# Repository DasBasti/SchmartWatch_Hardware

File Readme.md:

# Schmart Watch Hardware

## Table of Contents

- [Introduction](#introduction)
- [Terms of Use](#terms-of-use)
- [Problems?](#problems)
- [Changelog](#changelog)

## Introduction

This application is the hardware for the DIY Smartwatch project [Schmart Watch](http://www.kurzschluss-blog.de/2018/07/schmartwatch-01-smartwatch-selbst-gebaut.html).

To open the project you need [KiCad Version 5.0.0-rc2](http://kicad.org/) or newer.

## Terms of Use

Refer to "License.txt" for terms of use.

## Problems?

If you have any problems or questions, please ensure you have read this readme
file. If you are still having trouble, you can
[get in contact](https://plus.google.com/+BastianNeumann_DasBasti).

## Changelog

1. 2019-02-20: Version 0.1
  - Initial release of hardware version E3 for review

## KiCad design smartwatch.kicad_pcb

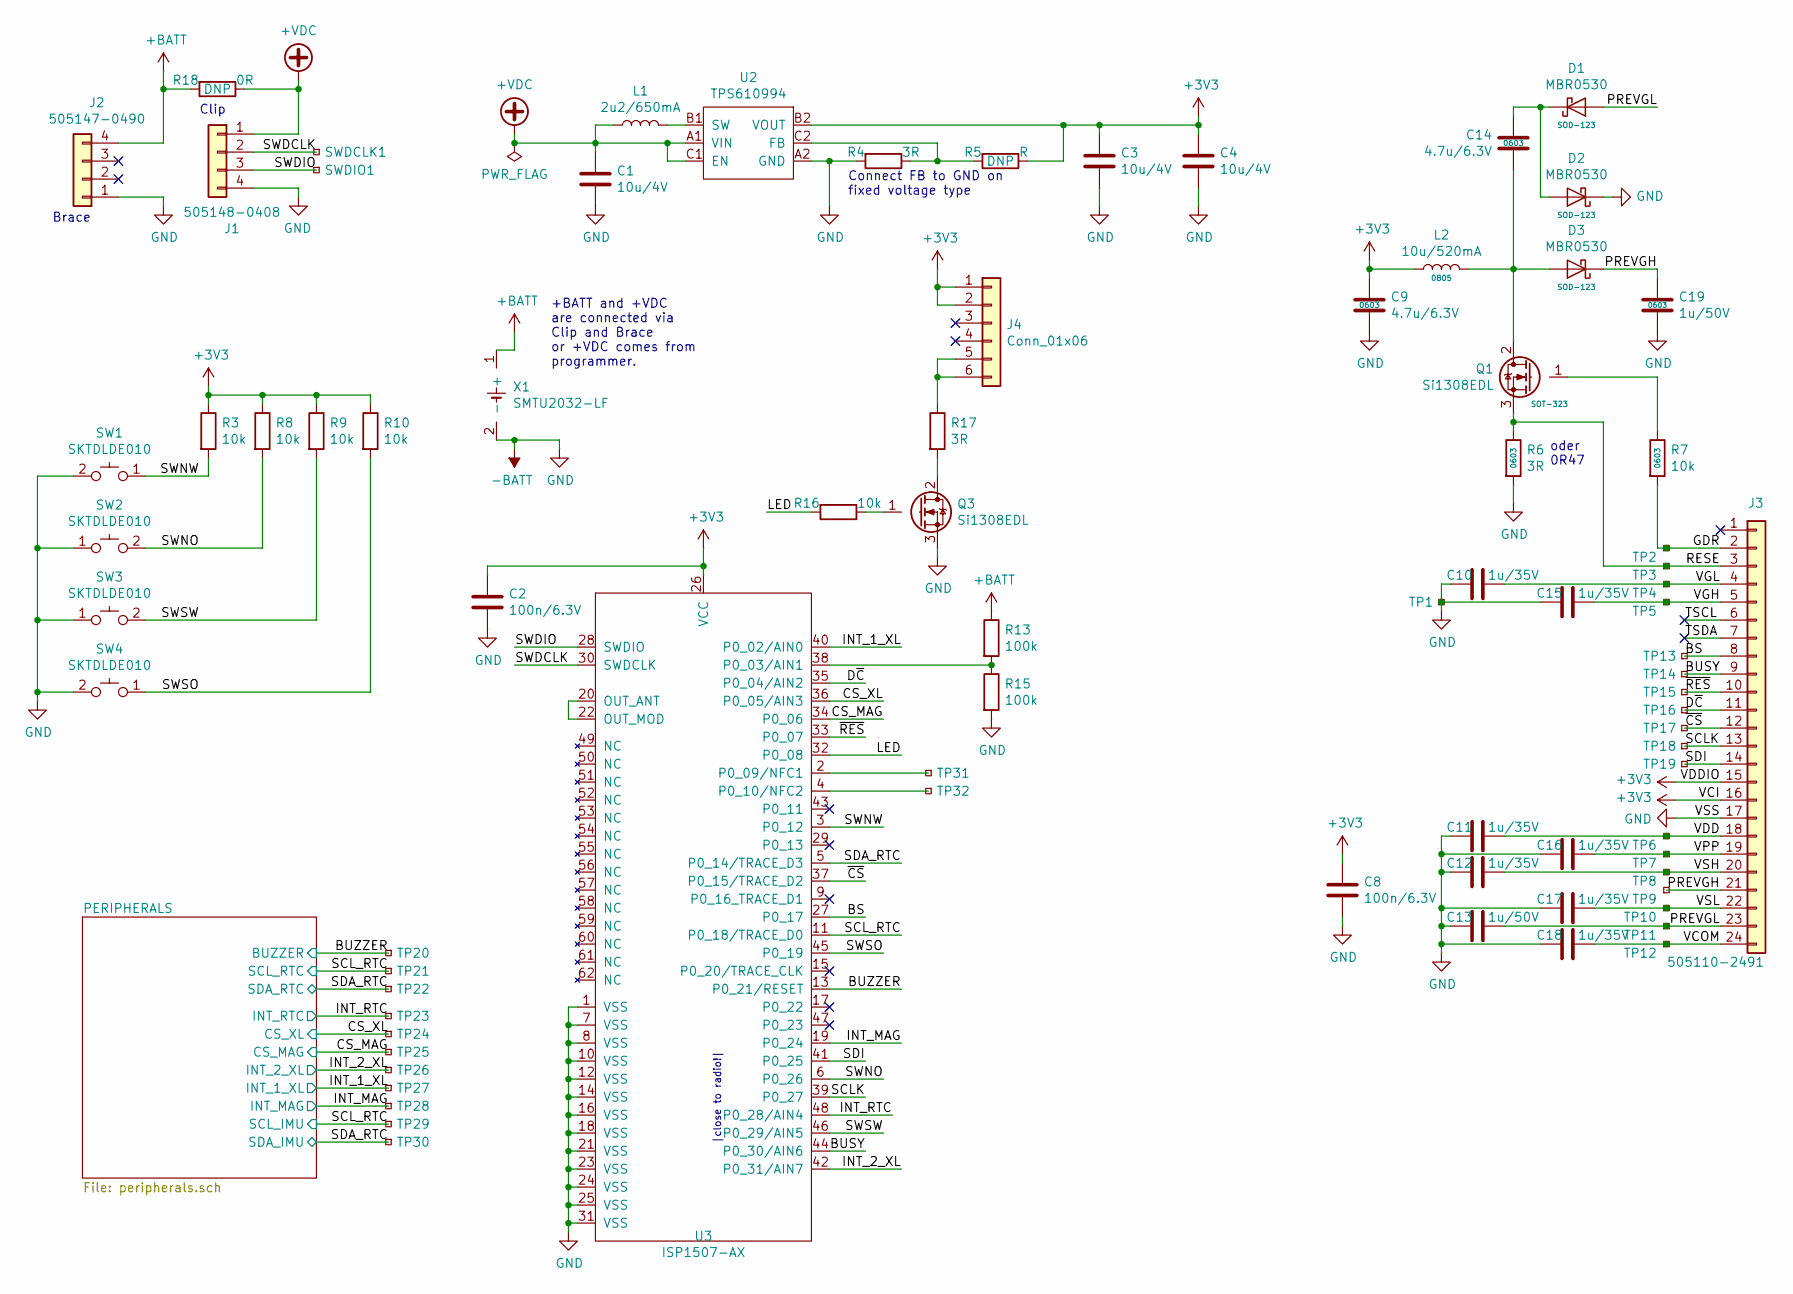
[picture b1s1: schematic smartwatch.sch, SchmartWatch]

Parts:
C1, C3, C4: 10u/4V; C_0603_1608Metric; MPN1 CL10A106MQ8NNNC
C2, C8: 100n/6.3V; C_0603_1608Metric; MPN1 GCM188R71C104KA37D
C9, C14: 4.7u/6.3V; C_0603_1608Metric; MPN1 GRT188C80J475ME01D
C10, C11, C12, C15, C16, C17, C18: 1u/35V; C_0603_1608Metric; MPN1 C1608X7R1V105K080AC
C13, C19: 1u/50V; C_0603_1608Metric; MPN1 GRT188R61H105KE13D
D1, D2, D3: MBR0530; D_SOD-123; MPN1 MBR0530
J1: 505148-0408; MPN1 505148-0408
J2: 505147-0490; 505147-0490_NO_SOLDER; MPN1 505147-0490
J3: 505110-2491; MOLEX_FPC_24_P0.5mm_505110-2491; MPN1 505110-2491
J4: Conn_01x06; 503480-0600; MPN1 503480-0600
L1: 2u2/650mA; L_0805_2012Metric; MPN1 MBKK2012T2R2M
L2: 10u/520mA; L_0805_2012Metric; MPN1 CB2012T100KR
Q1, Q3: Si1308EDL; SOT-323_SC-70; MPN1 SI1308EDL-T1-GE3
R3, R7, R8, R9, R10, R16: 10k; R_0603_1608Metric; MPN1 RMCF0603JG10K0
R4, R6, R17: 3R; R_0603_1608Metric; MPN1 RMCF0603JT3R00
R5: R; R_0603_1608Metric
R13, R15: 100k; R_0603_1608Metric; MPN1 RMCF0603JG100K
R18: 0R; R_0603_1608Metric
SW1, SW2, SW3, SW4: SKTDLDE010; MPN1 SKTDLDE010
SWDCLK1: TestPoint; TestPoint_Pad_D1.0mm
SWDIO1: TestPoint; TestPoint_Pad_D1.0mm
TP1, TP2, TP3, TP4, TP5, TP6, TP7, TP8, TP9, TP10, TP11, TP12, TP13, TP14, TP15, TP16, TP17, TP18, TP19, TP20, TP21, TP22, TP23, TP28, TP29, TP30: TestPoint; TestPoint_Pad_D1.0mm
TP24, TP25, TP26, TP27, TP31, TP32: TestPoint; TestPoint_Pad_D0.5mm
U2: TPS610994; BGA-6_2x3_1.0x1.35mm; MPN1 TPS610994
U3: ISP1507-AX; MPN1 ISP1507-AX
X1: SMTU2032-LF; SMTU2032-LF-6066; MPN1 SMTU2032-LF

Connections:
+3V3: C2.1, C3.1, C4.1, C8.1, C9.1, J3.15, J3.16, J3.25, J3.26, J4.1, J4.2, J4.7, J4.8, L2.1, R3.1, R5.1, R8.1, R9.1, R10.1, U2.B2 (VOUT), U3.26 (VCC); also elsewhere on the board
+BATT: J2.4, R13.1, R18.2, X1.1 (+); also elsewhere on the board
+VDC: C1.1, J1.1, L1.1, R18.1, U2.A1 (VIN), U2.C1 (EN)
-BATT: C1.2, C2.2, C3.2, C4.2, C8.2, C9.2, C10.2, C11.2, C12.2, C13.2, C15.2, C16.2, C17.2, C18.2, C19.2, D2.1 (K), J1.4, J2.1, J3.17, Q3.3 (S), R4.2, R6.2, R15.2, SW1.2, SW2.1, SW3.1, SW4.2, TP1.1, U2.A2 (GND), U3.1 (VSS), U3.7 (VSS), U3.8 (VSS), U3.10 (VSS), U3.12 (VSS), U3.14 (VSS), U3.16 (VSS), U3.18 (VSS), U3.21 (VSS), U3.23 (VSS), U3.24 (VSS), U3.25 (VSS), U3.31 (VSS), X1.2 (-); also elsewhere on the board
/BS: J3.8, TP13.1, U3.27 (P0_17)
/BUSY: J3.9, TP14.1, U3.44 (P0_30/AIN6)
/BUZZER: TP20.1, U3.13 (P0_21/RESET); also elsewhere on the board
/CS_MAG: TP25.1, U3.34 (P0_06); also elsewhere on the board
/CS_XL: TP24.1, U3.36 (P0_05/AIN3); also elsewhere on the board
/D~C: J3.11, TP16.1, U3.35 (P0_04/AIN2)
/GDR: J3.2, R7.2, TP2.1
/INT_1_XL: TP27.1, U3.40 (P0_02/AIN0); also elsewhere on the board
/INT_2_XL: TP26.1, U3.42 (P0_31/AIN7); also elsewhere on the board
/INT_MAG: TP28.1, U3.19 (P0_24); also elsewhere on the board
/INT_RTC: TP23.1, U3.48 (P0_28/AIN4); also elsewhere on the board
/LED: R16.2, U3.32 (P0_08)
/PREVGH: C19.1, D3.1 (K), J3.21, TP9.1
/PREVGL: C13.1, D1.2 (A), J3.23, TP11.1
/RESE: J3.3, Q1.3 (S), R6.1, TP3.1
/SCLK: J3.13, TP18.1, U3.39 (P0_27)
/SCL_RTC: TP21.1, TP29.1, U3.11 (P0_18/TRACE_D0); also elsewhere on the board
/SDA_RTC: TP22.1, TP30.1, U3.5 (P0_14/TRACE_D3); also elsewhere on the board
/SDI: J3.14, TP19.1, U3.41 (P0_25)
/SWDCLK: J1.2, SWDCLK1.1, U3.30 (SWDCLK)
/SWDIO: J1.3, SWDIO1.1, U3.28 (SWDIO)
/SWNO: R8.2, SW2.2, U3.6 (P0_26)
/SWNW: R3.2, SW1.1, U3.3 (P0_12)
/SWSO: R10.2, SW4.1, U3.45 (P0_19)
/SWSW: R9.2, SW3.2, U3.46 (P0_29/AIN5)
/TSCL: J3.6
/TSDA: J3.7
/VCOM: C18.1, J3.24, TP12.1
/VDD: C11.1, J3.18, TP6.1
/VGH: C15.1, J3.5, TP5.1
/VGL: C10.1, J3.4, TP4.1
/VPP: C16.1, J3.19, TP7.1
/VSH: C12.1, J3.20, TP8.1
/VSL: C17.1, J3.22, TP10.1
/~CS: J3.12, TP17.1, U3.37 (P0_15/TRACE_D2)
/~RES: J3.10, TP15.1, U3.33 (P0_07)
unnamed: C14.1, D1.1 (K), D2.2 (A)
unnamed: C14.2, D3.2 (A), L2.2, Q1.2 (D)
unnamed 43: J2.2; also elsewhere on the board
unnamed 44: J2.3; also elsewhere on the board
unnamed: J4.5, J4.6, R17.1
unnamed: L1.2, U2.B1 (SW)
unnamed: Q1.1 (G), R7.1
unnamed: Q3.1 (G), R16.1
unnamed: Q3.2 (D), R17.2
unnamed: R4.1, R5.2, U2.C2 (FB)
unnamed: R13.2, R15.1, U3.38 (P0_03/AIN1)
unnamed: TP31.1, U3.2 (P0_09/NFC1)
unnamed: TP32.1, U3.4 (P0_10/NFC2)
unnamed: U3.20 (OUT_ANT), U3.22 (OUT_MOD)

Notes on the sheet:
|close to radio!|
oder 0R47
Clip
Brace
+BATT and +VDC are connected via Clip and Brace or +VDC comes from programmer.
Connect FB to GND on fixed voltage type

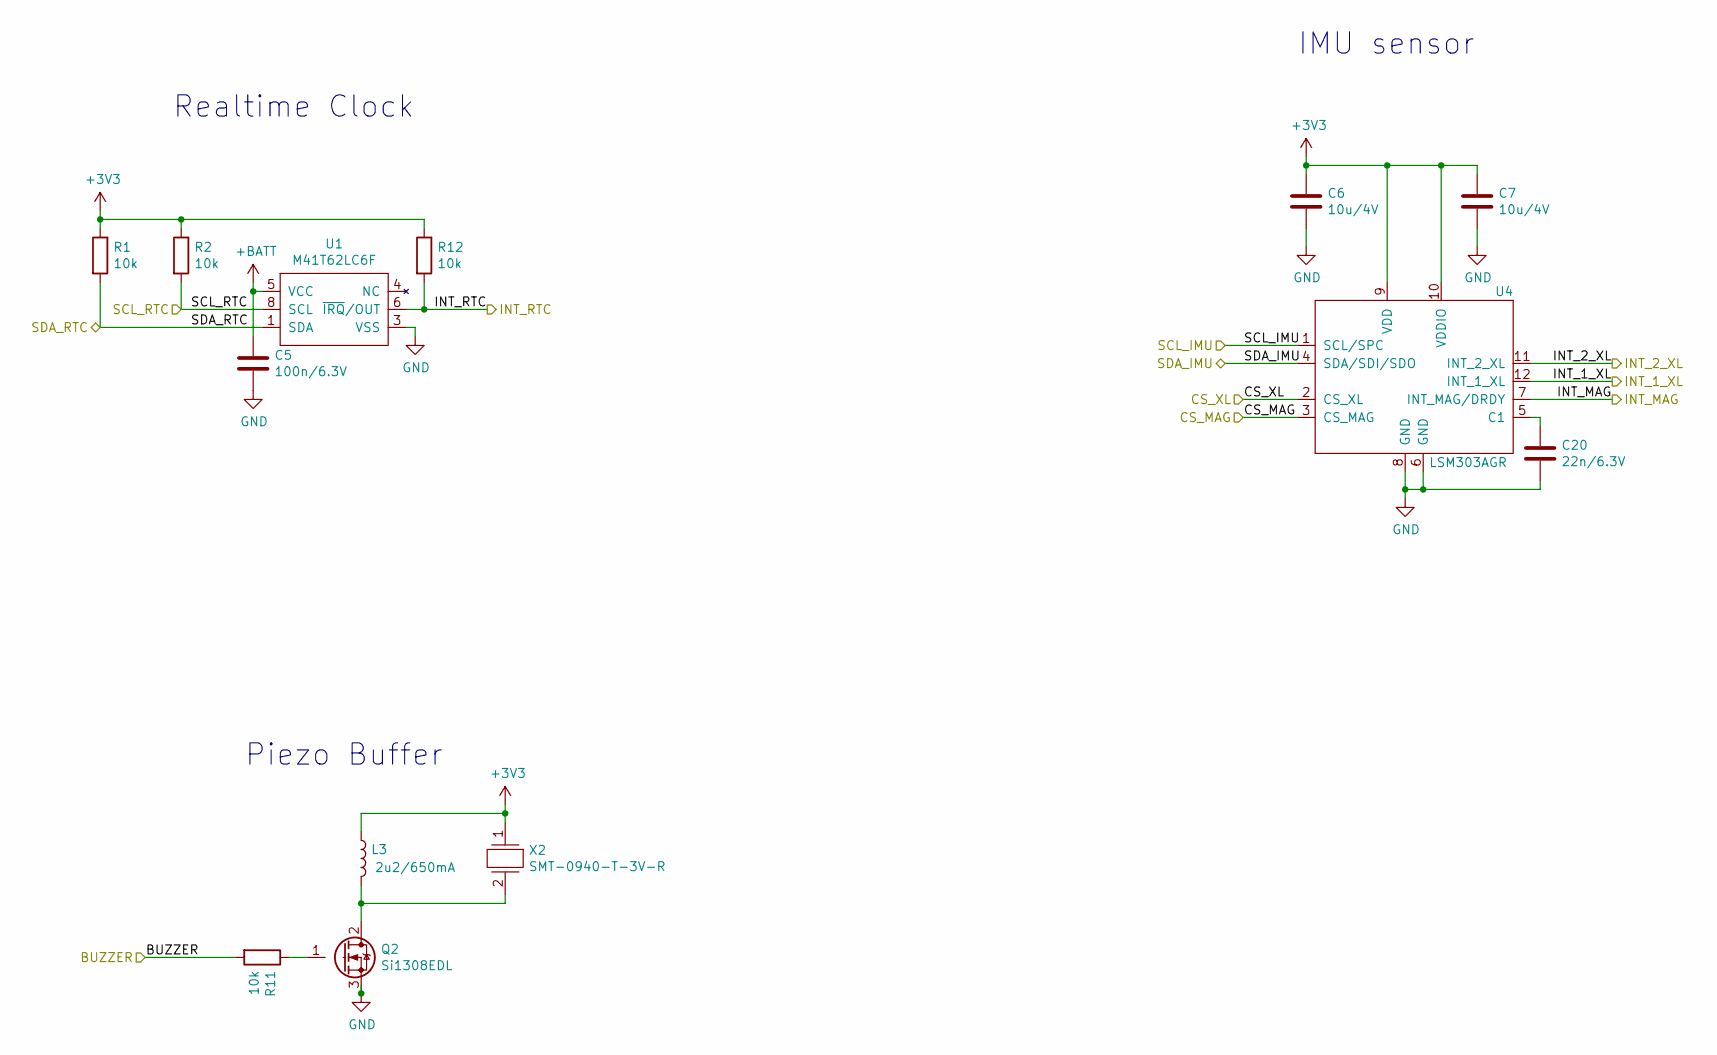
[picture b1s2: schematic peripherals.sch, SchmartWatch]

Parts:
C5: 100n/6.3V; C_0603_1608Metric; MPN1 GCM188R71C104KA37D
C6, C7: 10u/4V; C_0603_1608Metric; MPN1 CL10A106MQ8NNNC
C20: 22n/6.3V; C_0603_1608Metric; MPN1 GRM188R71H223KA01D
L3: 2u2/650mA; L_0805_2012Metric; MPN1 MBKK2012T2R2M
Q2: Si1308EDL; SOT-323_SC-70; MPN1 SI1308EDL-T1-GE3
R1, R2, R11, R12: 10k; R_0603_1608Metric; MPN1 RMCF0603JG10K0
U1: M41T62LC6F; LCC-8_1.5x3.2mm_P0.9mm; MPN1 M41T62LC6F
U4: LSM303AGR; LGA-12_2x2mm_P0.5mm; MPN1 LSM303AGR
X2: SMT-0940-T-3V-R; SMT-0940-T_3V-R; MPN1 SMT-0940-T-3V-R

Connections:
+3V3: C6.1, C7.1, L3.1, R1.1, R2.1, R12.1, U4.9 (VDD), U4.10 (VDDIO), X2.1; also elsewhere on the board
+BATT: C5.1, U1.5 (VCC); also elsewhere on the board
-BATT: C5.2, C6.2, C7.2, C20.2, Q2.3 (S), U1.3 (VSS), U4.6 (GND), U4.8 (GND); also elsewhere on the board
/BUZZER: R11.2; also elsewhere on the board
/CS_MAG: U4.3 (CS_MAG); also elsewhere on the board
/CS_XL: U4.2 (CS_XL); also elsewhere on the board
/INT_1_XL: U4.12 (INT_1_XL); also elsewhere on the board
/INT_2_XL: U4.11 (INT_2_XL); also elsewhere on the board
/INT_MAG: U4.7 (INT_MAG/DRDY); also elsewhere on the board
/INT_RTC: R12.2, U1.6 (~IRQ~/OUT); also elsewhere on the board
/SCL_RTC: R2.2, U1.8 (SCL), U4.1 (SCL/SPC); also elsewhere on the board
/SDA_RTC: R1.2, U1.1 (SDA), U4.4 (SDA/SDI/SDO); also elsewhere on the board
unnamed: C20.1, U4.5 (C1)
unnamed: L3.2, Q2.2 (D), X2.2
unnamed: Q2.1 (G), R11.1

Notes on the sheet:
Realtime Clock
IMU sensor
Piezo Buffer

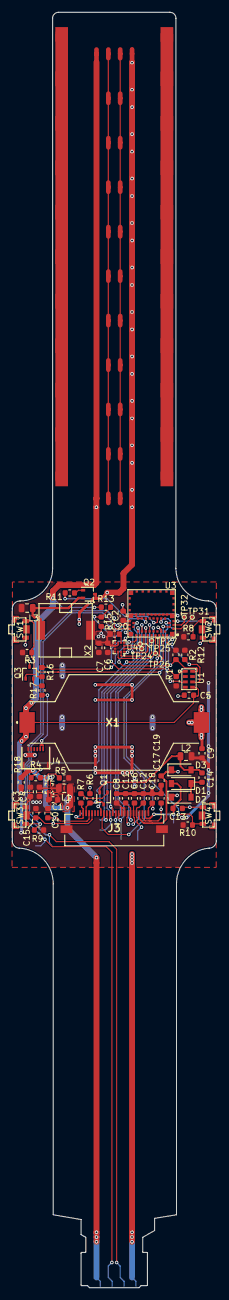
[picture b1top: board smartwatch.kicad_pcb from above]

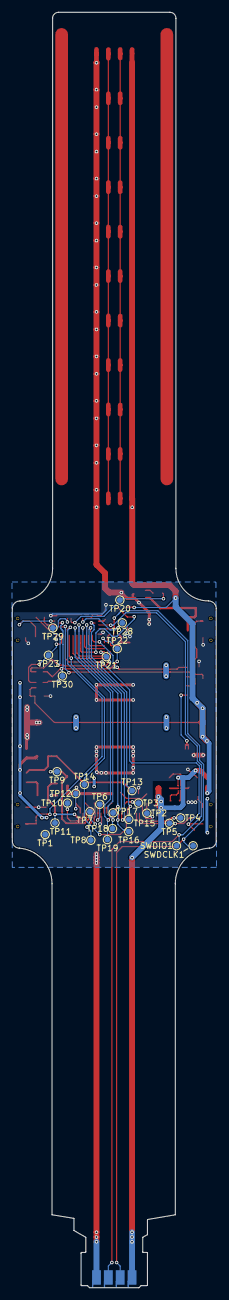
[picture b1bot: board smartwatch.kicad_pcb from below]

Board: 2 copper layers, 34.4 x 215.2 mm, 104 parts (29 on the bottom side), 55 nets.

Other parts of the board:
J2#2, J2#3, J2#4, J2#5, J2#6, J2#7, J2#8, J2#9, J2#10, J2#11: 505147-0490; 505147-0490_NO_SOLDER

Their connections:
+BATT: J2#2.4, J2#3.4, J2#4.4, J2#5.4, J2#6.4, J2#7.4, J2#8.4, J2#9.4, J2#10.4, J2#11.4; also elsewhere on the board
-BATT: J2#2.1, J2#3.1, J2#4.1, J2#5.1, J2#6.1, J2#7.1, J2#8.1, J2#9.1, J2#10.1, J2#11.1; also elsewhere on the board
unnamed 43: J2#2.2, J2#3.2, J2#4.2, J2#5.2, J2#6.2, J2#7.2, J2#8.2, J2#9.2, J2#10.2, J2#11.2; also elsewhere on the board
unnamed 44: J2#2.3, J2#3.3, J2#4.3, J2#5.3, J2#6.3, J2#7.3, J2#8.3, J2#9.3, J2#10.3, J2#11.3; also elsewhere on the board

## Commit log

2019-02-20 initial commit for review
2019-02-20 add schematic PDF
2019-02-20 Add layout PDF
2019-02-20 move R18 reference so it does not overlap with C3 and C4
2019-02-20 J3 and J4 SMD mounting pads are connected to +3V3 plane for stability. X2 is rotated to be alongside the bend radious if watch is worn. also for stability. traces leading to buzzer are thickened for 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
2019-02-20 connect solder tabs of clasp connector J2 to plane for stability. pads are connected with thermal relief for easy soldering
2019-02-20 Fix: put L1 closer to SW pin of TPS610994; add more vias to power traces
2019-02-20 Fix: move via to close 3V3 plane next to batt+ voltage line.
2019-02-20 Fix: increase -BATT thickness for capacitor bank of display.
2019-02-21 FIX: increase thickness of traces on wristband clasp so the pads extend under the solder resist.
2019-02-21 Add render of PCB
2019-02-23 remove plane from wristband for better flexibility (OSHPark recommendation)
2021-11-09 Update Readme.md
    https://forum.kicad.info/t/warning-avoid-all-links-to-kicad-pcb-org-use-kicad-org/31521
